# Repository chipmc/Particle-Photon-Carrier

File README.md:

# Particle-Photon-Carrier
EAGLE design files for the Particle Carrier

This is a project that implements a smart watering system for back-deck gardening.  I use the Particle platform
to moniror the soil moisture and the near-tearm weather forecast to amek intelligent decisions on when and how
much to water.  I have used this system on my own garden for the past three years and each year it gets a little better.

Please see the full project description and documentation (hardware and software) on Hackster.io.  

Here is the project link: https://www.hackster.io/chipmc/smart-and-safe-outdoor-plant-watering-system-new-for-2018

And keep an eye out for annual updates.

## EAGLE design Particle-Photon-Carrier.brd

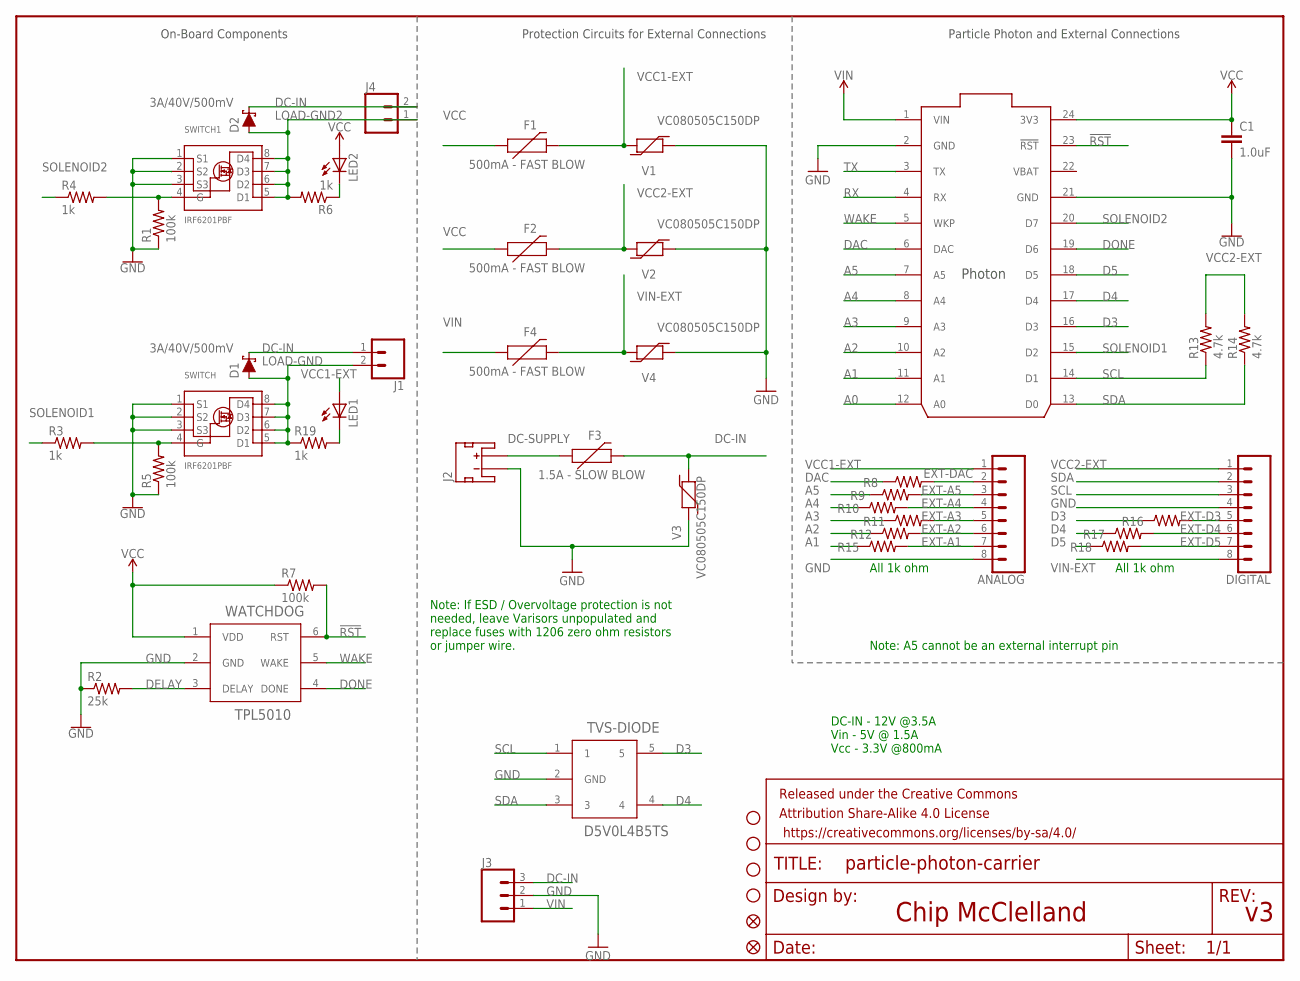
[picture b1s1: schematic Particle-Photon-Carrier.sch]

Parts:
ANALOG: CONN_083.5MM-8; SCREWTERMINAL-3.5MM-8
C1: 1.0uF; 0805
D1, D2: 3A/40V/500mV; SMA-DIODE
DIGITAL: CONN_083.5MM-8; SCREWTERMINAL-3.5MM-8
F1, F2, F4: 500mA - FAST BLOW; 1206
F3: 1.5A - SLOW BLOW; 1206
FD1, FD2: FIDUCIALUFIDUCIAL; FIDUCIAL-MICRO
FRAME1: FRAME-LETTER; CREATIVE_COMMONS
J1, J4: CONN_023.5MM; SCREWTERMINAL-3.5MM-2
J2: 5V @ 2A; JST-2-SMD
J3: CONN_03LOCK; 1X03_LOCK
JP3, JP4, JP5, JP6: STAND-OFF
LED1, LED2: LEDCHIPLED_0805; CHIPLED_0805
PHOTON: PHOTON_WITH_HEADERS; PHOTON
R1, R5, R7: 100k; R0805
R2: 25k; R0805
R3, R4, R6, R8, R9, R10, R11, R12, R15, R16, R17, R18, R19: 1k; R0805
R13, R14: 4.7k; R0805
SWITCH, SWITCH1: IRF6201PBF; SO8-GW300
TVS-DIODE: D5V0L4B5TS; SOT-23-5
V1, V2, V3, V4: VC080505C150DP; 0805
WATCHDOG: TPL5010; TSOT-23

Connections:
!RST: PHOTON.23 (!RST), R7.2, WATCHDOG.6 (RST)
A0: PHOTON.12 (A0)
A1: PHOTON.11 (A1), R15.1
A2: PHOTON.10 (A2), R12.1
A3: PHOTON.9 (A3), R11.1
A4: PHOTON.8 (A4), R10.1
A5: PHOTON.7 (A5), R9.1
D3: PHOTON.16 (D3), R16.1, TVS-DIODE.5
D4: PHOTON.17 (D4), R17.1, TVS-DIODE.4
D5: PHOTON.18 (D5), R18.1
DAC: PHOTON.6 (DAC), R8.1
DC-IN: D1.C, D2.C, F3.2, J1.1, J3.3, J4.2, V3.2
DC-SUPPLY: F3.1, J2.2 (+)
DELAY: R2.2, WATCHDOG.3 (DELAY)
DONE: PHOTON.19 (D6), WATCHDOG.4 (DONE)
EXT-A1: ANALOG.7, R15.2
EXT-A2: ANALOG.6, R12.2
EXT-A3: ANALOG.5, R11.2
EXT-A4: ANALOG.4, R10.2
EXT-A5: ANALOG.3, R9.2
EXT-D3: DIGITAL.5, R16.2
EXT-D4: DIGITAL.6, R17.2
EXT-D5: DIGITAL.7, R18.2
EXT-DAC: ANALOG.2, R8.2
GATE: R3.2, R5.2, SWITCH.4 (G)
GATE1: R1.2, R4.2, SWITCH1.4 (G)
GND: ANALOG.8, C1.2, DIGITAL.4, J2.1 (-), J3.2, PHOTON.2 (GND), PHOTON.21 (GND), R1.1, R2.1, R5.1, SWITCH.1 (S1), SWITCH.2 (S2), SWITCH.3 (S3), SWITCH1.1 (S1), SWITCH1.2 (S2), SWITCH1.3 (S3), TVS-DIODE.2 (GND), V1.1, V2.1, V3.1, V4.1, WATCHDOG.2 (GND)
LOAD-GND: D1.A, J1.2, R19.1, SWITCH.5 (D1), SWITCH.6 (D2), SWITCH.7 (D3), SWITCH.8 (D4)
LOAD-GND2: D2.A, J4.1, R6.2, SWITCH1.5 (D1), SWITCH1.6 (D2), SWITCH1.7 (D3), SWITCH1.8 (D4)
unnamed: LED2.C, R6.1
unnamed: LED1.C, R19.2
RX: PHOTON.4 (RX)
SCL: DIGITAL.3, PHOTON.14 (D1), R13.1, TVS-DIODE.1
SDA: DIGITAL.2, PHOTON.13 (D0), R14.1, TVS-DIODE.3
SOLENOID1: PHOTON.15 (D2), R3.1
SOLENOID2: PHOTON.20 (D7), R4.1
TX: PHOTON.3 (TX)
VBAT: PHOTON.22 (VBAT)
VCC: C1.1, F1.1, F2.1, LED2.A, PHOTON.24 (3V3), R7.1, WATCHDOG.1 (VDD)
VCC1-EXT: ANALOG.1, F1.2, LED1.A, V1.2
VCC2-EXT: DIGITAL.1, F2.2, R13.2, R14.2, V2.2
VIN: F4.1, J3.1, PHOTON.1 (VIN)
VIN-EXT: DIGITAL.8, F4.2, V4.2
WAKE: PHOTON.5 (WKP), WATCHDOG.5 (WAKE)

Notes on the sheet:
Chip McClelland
Note: A5 cannot be an external interrupt pin
DC-IN - 12V @3.5A Vin - 5V @ 1.5A Vcc - 3.3V @800mA
Protection Circuits for External Connections
On-Board Components
Particle Photon and External Connections
Note: If ESD / Overvoltage protection is not needed, leave Varisors unpopulated and replace fuses with 1206 zero ohm resistors or jumper wire.
All 1k ohm

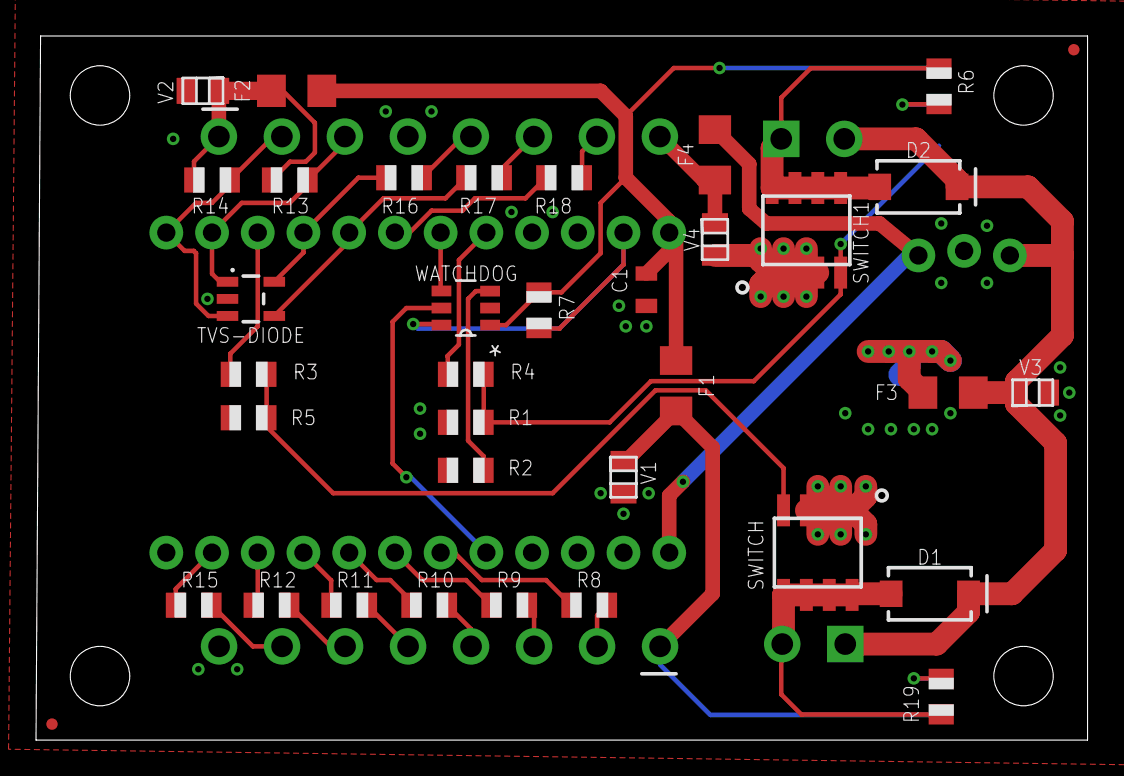
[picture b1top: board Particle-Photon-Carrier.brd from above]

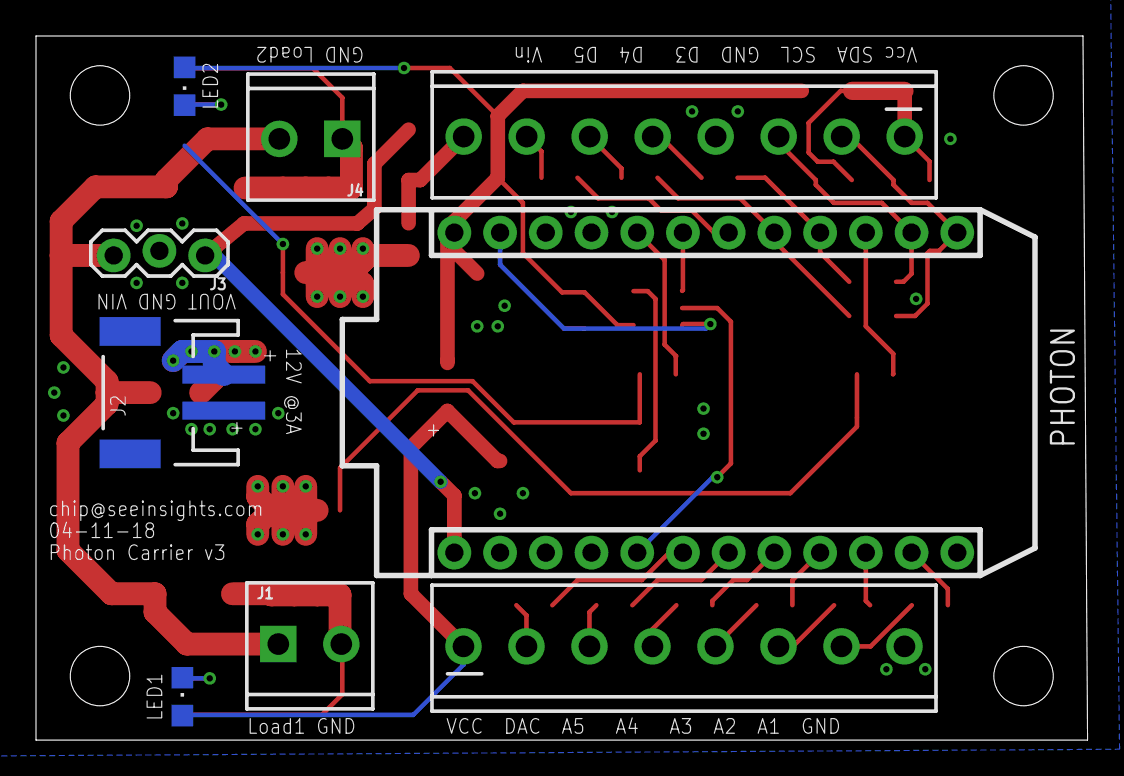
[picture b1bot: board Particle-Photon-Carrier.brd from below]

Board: 2 copper layers, 58.4 x 39.1 mm, 50 parts (9 on the bottom side), 40 nets.

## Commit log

2017-08-23 Carrier board for the Particle Photon
2017-08-23 Latest AquaMaster Carrier Board - sent to OSHPark today
2017-11-08 Added BOM
2017-11-08 edited gitignore
2017-11-08 Deleted
2017-11-08 Updated BOM
2017-11-08 Added Header Part numbers
2018-04-13 v3 of the AquaMaster
    For Spring 2018
2018-04-13 New files
2019-05-01 Deleted old BOM and added the new

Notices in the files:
parts and their libraries:
Particle-Devices: Licensing: Designed by Particle.
SparkFun-Connectors: Licensing: Creative Commons ShareAlike 4.0 International - https://creativecommons.org/licenses/by-sa/4.0
SparkFun-Aesthetics: Released under the Creative Commons Attribution Share-Alike 4.0 License
